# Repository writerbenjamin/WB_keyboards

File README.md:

# WB_keyboards
These are keyboards that I've designed.

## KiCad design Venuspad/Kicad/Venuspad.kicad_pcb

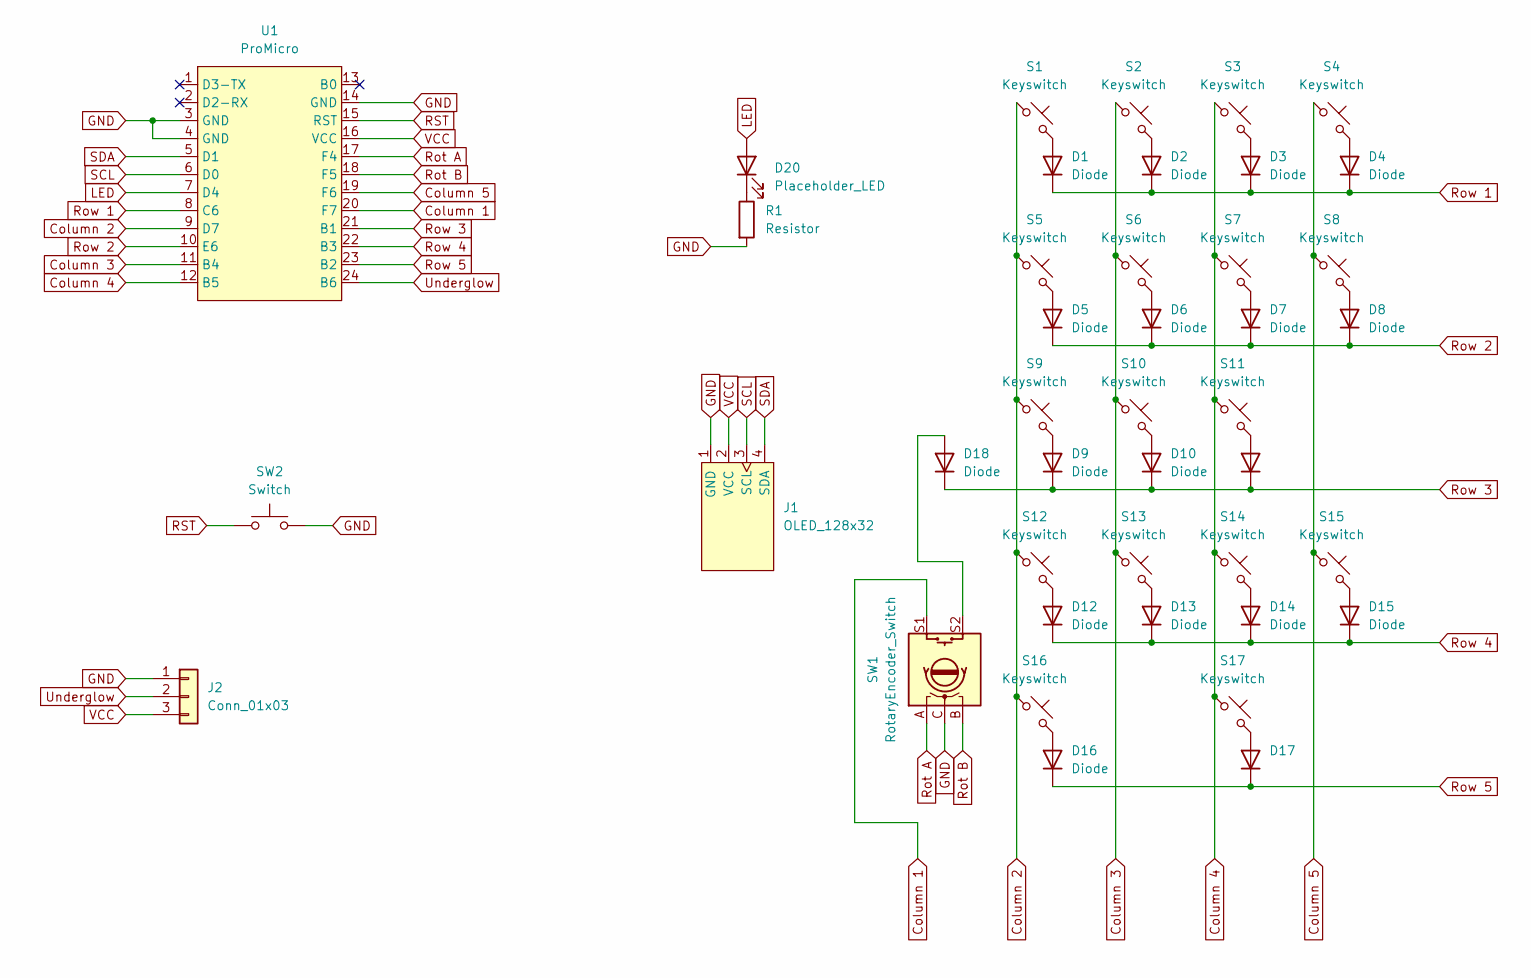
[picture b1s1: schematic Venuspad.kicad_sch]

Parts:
D1, D2, D3, D4, D5, D6, D7, D8, D9, D10, D11, D12, D13, D14, D15, D16, D17, D18: Diode; Diode_DO-35
D20: Placeholder_LED; LED_MX_3mm
J1: OLED_128x32
J2: Conn_01x03; PinHeader_1x03_P2.54mm_Vertical
R1: Resistor; R_Axial_DIN0207_L6.3mm_D2.5mm_P7.62mm_Horizontal
S1, S2, S3, S4, S5, S6, S7, S9, S10, S11, S12, S13, S14, S16: Keyswitch; Hotswap_MX_Plated_1.00u
S8, S15: Keyswitch; Hotswap_MX_Plated_2.00u_90deg
S17: Keyswitch; Hotswap_MX_Plated_2.00u
SW1: RotaryEncoder_Switch; Encoder_EC11_MX
SW2: Switch; Button_TL3342
U1: ProMicro; ProMicro_USBdn

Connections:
Column 1: SW1.S1, U1.20 (F7)
Column 2: S1.1, S5.1, S9.1, S12.1, S16.1, U1.9 (D7)
Column 3: S2.1, S6.1, S10.1, S13.1, U1.11 (B4)
Column 4: S3.1, S7.1, S11.1, S14.1, S17.1, U1.12 (B5)
Column 5: S4.1, S8.1, S15.1, U1.19 (F6)
GND: J1.1 (GND), J2.1, R1.2, SW1.C, SW2.2, U1.3 (GND), U1.4 (GND), U1.14 (GND)
LED: D20.2 (A), U1.7 (D4)
unnamed: D1.2 (A), S1.2
unnamed: D2.2 (A), S2.2
unnamed: D3.2 (A), S3.2
unnamed: D4.2 (A), S4.2
unnamed: D5.2 (A), S5.2
unnamed: D6.2 (A), S6.2
unnamed: D7.2 (A), S7.2
unnamed: D8.2 (A), S8.2
unnamed: D9.2 (A), S9.2
unnamed: D10.2 (A), S10.2
unnamed: D11.2 (A), S11.2
unnamed: D12.2 (A), S12.2
unnamed: D13.2 (A), S13.2
unnamed: D14.2 (A), S14.2
unnamed: D15.2 (A), S15.2
unnamed: D16.2 (A), S16.2
unnamed: D17.2 (A), S17.2
unnamed: D18.2 (A), SW1.S2
unnamed: D20.1 (K), R1.1
RST: SW2.1, U1.15 (RST)
Rot A: SW1.A, U1.17 (F4)
Rot B: SW1.B, U1.18 (F5)
Row 1: D1.1 (K), D2.1 (K), D3.1 (K), D4.1 (K), U1.8 (C6)
Row 2: D5.1 (K), D6.1 (K), D7.1 (K), D8.1 (K), U1.10 (E6)
Row 3: D9.1 (K), D10.1 (K), D11.1 (K), D18.1 (K), U1.21 (B1)
Row 4: D12.1 (K), D13.1 (K), D14.1 (K), D15.1 (K), U1.22 (B3)
Row 5: D16.1 (K), D17.1 (K), U1.23 (B2)
SCL: J1.3 (SCL), U1.6 (D0)
SDA: J1.4 (SDA), U1.5 (D1)
Underglow: J2.2, U1.24 (B6)
VCC: J1.2 (VCC), J2.3, U1.16 (VCC)

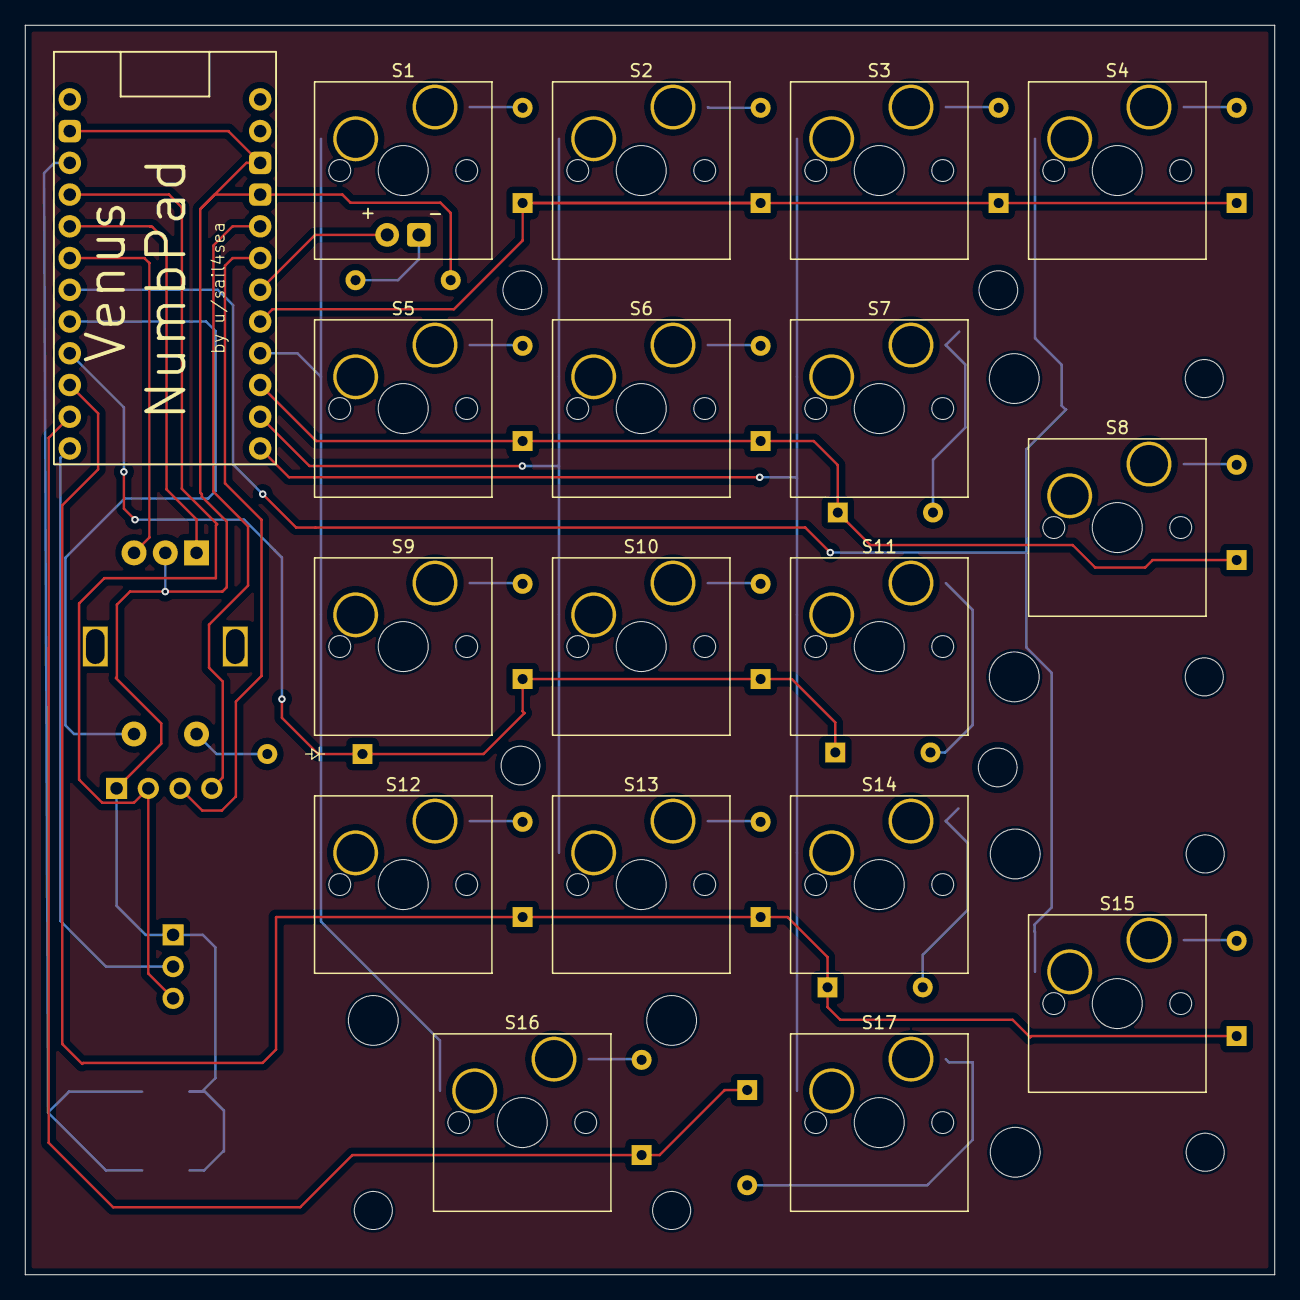
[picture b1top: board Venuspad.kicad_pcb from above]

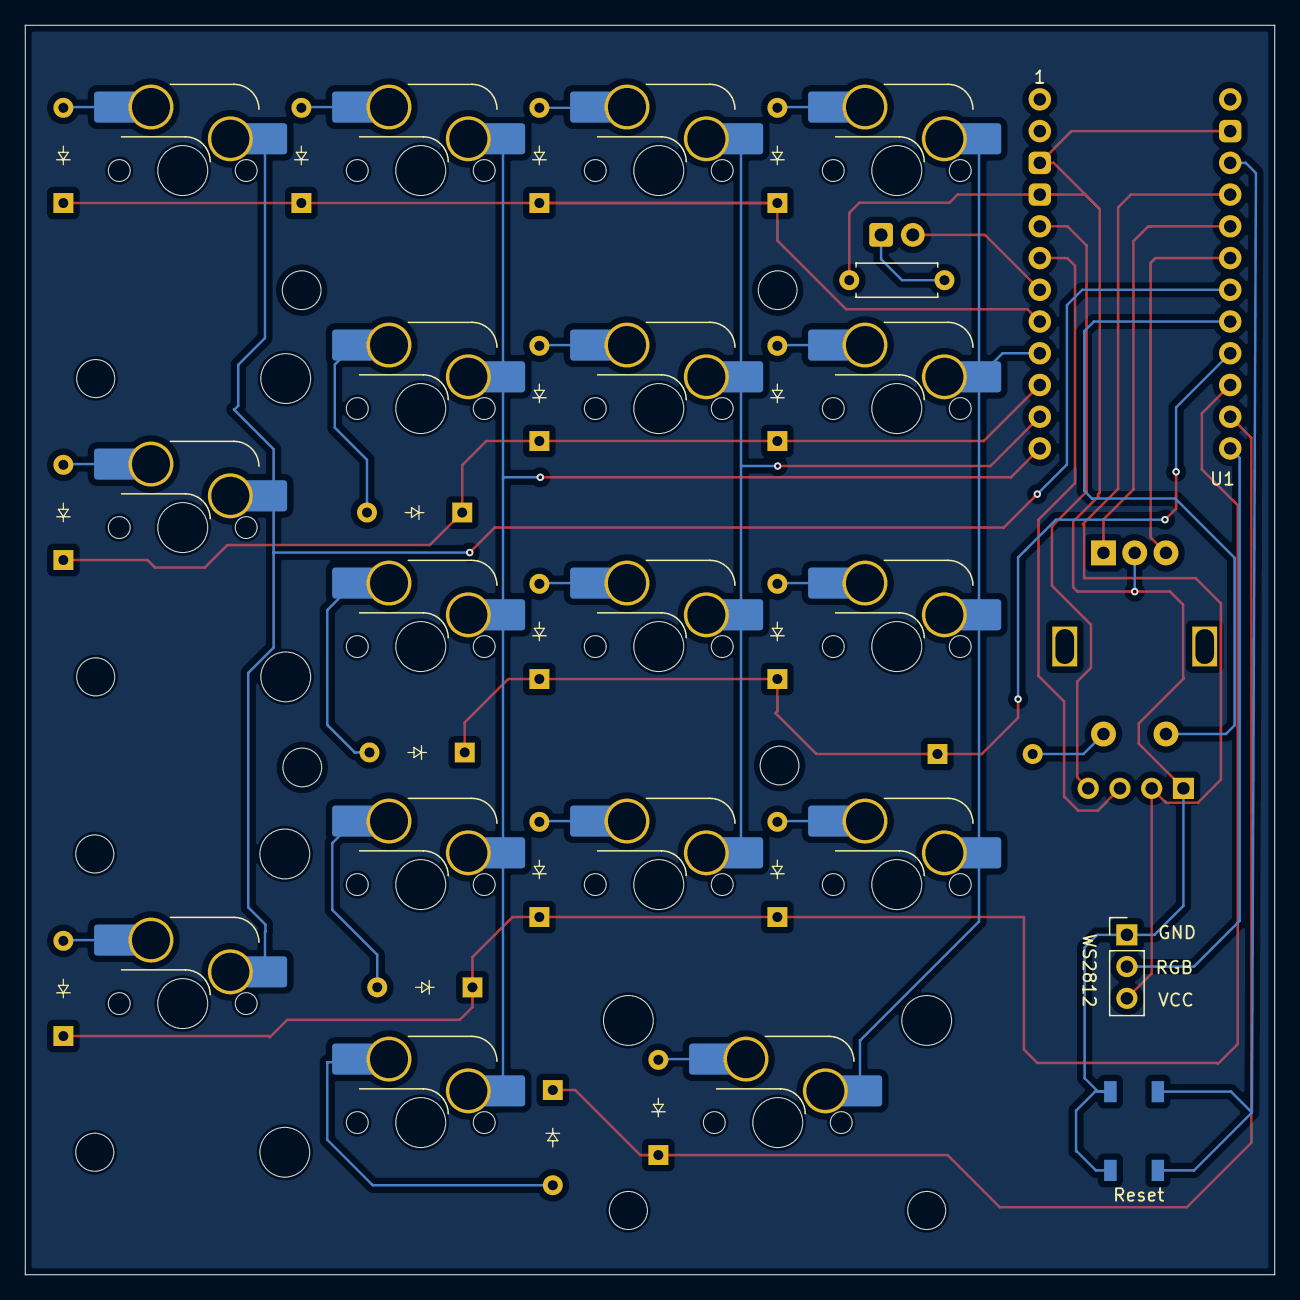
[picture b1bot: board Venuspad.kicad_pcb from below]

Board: 2 copper layers, 100.0 x 100.0 mm, 42 parts (20 on the bottom side), 38 nets.

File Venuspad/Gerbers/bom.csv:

Designator,Footprint,Quantity,Value,LCSC Part #
"D1, D10, D11, D12, D13, D14, D15, D16, D17, D18, D2, D3, D4, D5, D6, D7, D8, D9",Diode_DO-35,18,Diode,
D20,LED_MX_3mm,1,Placeholder_LED,
J1,OLED_128x32,1,OLED_128x32,
J2,PinHeader_1x03_P2.54mm_Vertical,1,Conn_01x03,
R1,R_Axial_DIN0207_L6.3mm_D2.5mm_P7.62mm_Horizontal,1,Resistor,
"S1, S10, S11, S12, S13, S14, S16, S2, S3, S4, S5, S6, S7, S9",Hotswap_MX_Plated_1.00u,14,Keyswitch,
"S15, S8",Hotswap_MX_Plated_2.00u_90deg,2,Keyswitch,
S17,Hotswap_MX_Plated_2.00u,1,Keyswitch,
SW1,Encoder_EC11_MX,1,RotaryEncoder_Switch,
SW2,Button_TL3342,1,Switch,

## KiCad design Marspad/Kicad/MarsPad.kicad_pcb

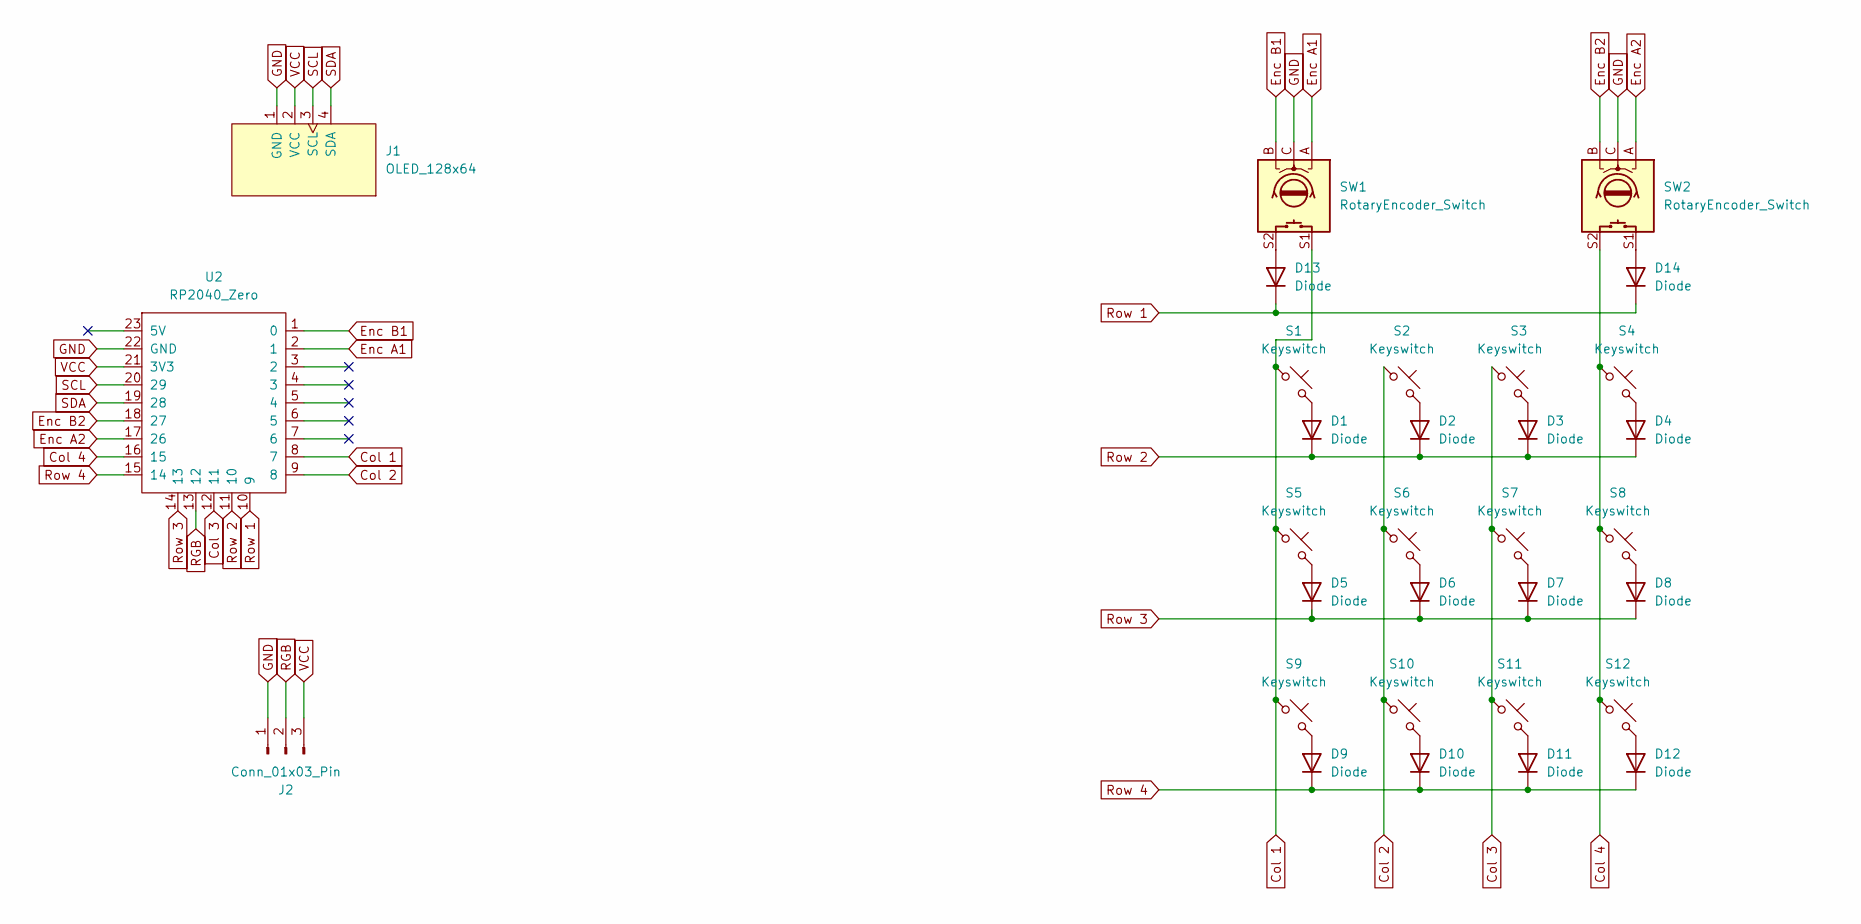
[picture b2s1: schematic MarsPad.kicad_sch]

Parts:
D1, D2, D3, D4, D5, D6, D7, D8, D9, D10, D11, D12, D13, D14: Diode; Diode_DO-35
J1: OLED_128x64; OLED_128x32
J2: Conn_01x03_Pin; PinSocket_1x03_P2.54mm_Vertical
S1, S2, S3, S4, S5, S6, S7, S8, S9, S10, S11, S12: Keyswitch; Hotswap_MX_1.00u
SW1, SW2: RotaryEncoder_Switch; Encoder_EC11_MX
U2: RP2040_Zero

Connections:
Col 1: S1.1, S5.1, S9.1, SW1.S1, U2.8 (7)
Col 2: S2.1, S6.1, S10.1, U2.9 (8)
Col 3: S3.1, S7.1, S11.1, U2.12 (11)
Col 4: S4.1, S8.1, S12.1, SW2.S2, U2.16 (15)
Enc A1: SW1.A, U2.2 (1)
Enc A2: SW2.A, U2.17 (26)
Enc B1: SW1.B, U2.1 (0)
Enc B2: SW2.B, U2.18 (27)
GND: J1.1 (GND), J2.1, SW1.C, SW2.C, U2.22 (GND)
unnamed: D1.2 (A), S1.2
unnamed: D2.2 (A), S2.2
unnamed: D3.2 (A), S3.2
unnamed: D4.2 (A), S4.2
unnamed: D5.2 (A), S5.2
unnamed: D6.2 (A), S6.2
unnamed: D7.2 (A), S7.2
unnamed: D8.2 (A), S8.2
unnamed: D9.2 (A), S9.2
unnamed: D10.2 (A), S10.2
unnamed: D11.2 (A), S11.2
unnamed: D12.2 (A), S12.2
unnamed: D13.2 (A), SW1.S2
unnamed: D14.2 (A), SW2.S1
RGB: J2.2, U2.13 (12)
Row 1: D13.1 (K), D14.1 (K), U2.10 (9)
Row 2: D1.1 (K), D2.1 (K), D3.1 (K), D4.1 (K), U2.11 (10)
Row 3: D5.1 (K), D6.1 (K), D7.1 (K), D8.1 (K), U2.14 (13)
Row 4: D9.1 (K), D10.1 (K), D11.1 (K), D12.1 (K), U2.15 (14)
SCL: J1.3 (SCL), U2.20 (29)
SDA: J1.4 (SDA), U2.19 (28)
VCC: J1.2 (VCC), J2.3, U2.21 (3V3)

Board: 2 copper layers, 31 parts (16 on the bottom side), 31 nets, no tracks yet.

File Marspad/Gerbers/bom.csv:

Designator,Footprint,Quantity,Value,LCSC Part #
"D1, D10, D11, D12, D13, D14, D2, D3, D4, D5, D6, D7, D8, D9",Diode_DO-35,14,Diode,
J1,OLED_128x32,1,OLED_128x64,
J2,PinSocket_1x03_P2.54mm_Vertical,1,Conn_01x03_Pin,
"S1, S10, S11, S12, S2, S3, S4, S5, S6, S7, S8, S9",Hotswap_MX_1.00u,12,Keyswitch,
"SW1, SW2",Encoder_EC11_MX,2,RotaryEncoder_Switch,
U2,RP2040_Zero,1,RP2040_Zero,

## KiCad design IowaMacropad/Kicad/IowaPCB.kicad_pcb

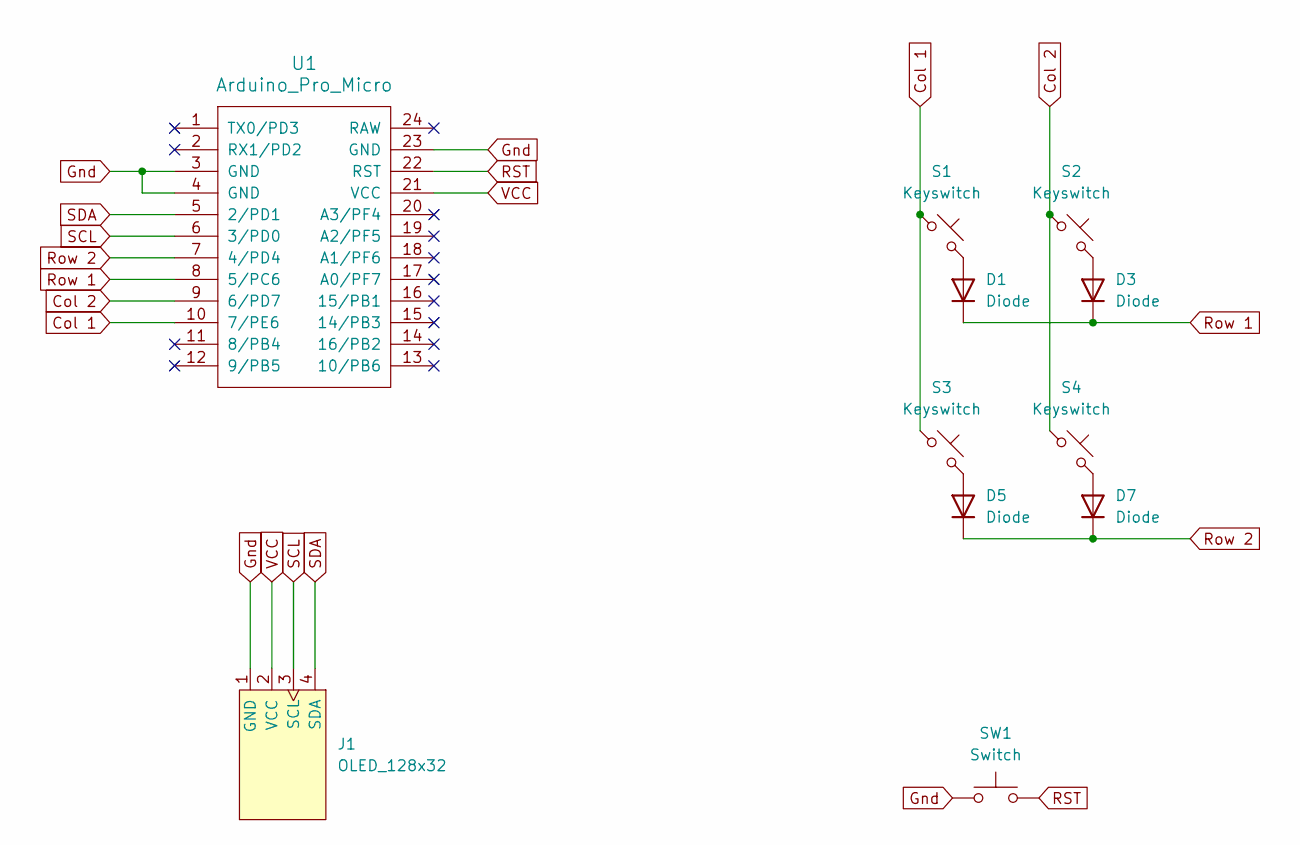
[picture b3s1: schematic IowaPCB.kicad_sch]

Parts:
D1, D3, D5, D7: Diode; Diode_DO-35
J1: OLED_128x32
S1: Keyswitch; MX_Plate_ISOEnter_180deg
S2, S3: Keyswitch; MX_PCB_1.00u
S4: Keyswitch; MX_Plate_ISOEnter
SW1: Switch; Button_TL3342
U1: Arduino_Pro_Micro

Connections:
Col 1: S1.1, S3.1, U1.10 (7/PE6)
Col 2: S2.1, S4.1, U1.9 (6/PD7)
Gnd: J1.1 (GND), SW1.1, U1.3 (GND), U1.4 (GND), U1.23 (GND)
unnamed: D1.2 (A), S1.2
unnamed: D3.2 (A), S2.2
unnamed: D5.2 (A), S3.2
unnamed: D7.2 (A), S4.2
RST: SW1.2, U1.22 (RST)
Row 1: D1.1 (K), D3.1 (K), U1.8 (5/PC6)
Row 2: D5.1 (K), D7.1 (K), U1.7 (4/PD4)
SCL: J1.3 (SCL), U1.6 (3/PD0)
SDA: J1.4 (SDA), U1.5 (2/PD1)
VCC: J1.2 (VCC), U1.21 (VCC)

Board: 2 copper layers, 11 parts (6 on the bottom side), 13 nets, no tracks yet.

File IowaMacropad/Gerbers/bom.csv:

Designator,Footprint,Quantity,Value,LCSC Part #
"D1, D3, D5, D7",Diode_DO-35,4,Diode,
J1,OLED_128x32,1,OLED_128x32,
S1,MX_Plate_ISOEnter_180deg,1,Keyswitch,
"S2, S3",MX_PCB_1.00u,2,Keyswitch,
S4,MX_Plate_ISOEnter,1,Keyswitch,
SW1,Button_TL3342,1,Switch,
U1,Arduino_Pro_Micro,1,Arduino_Pro_Micro,

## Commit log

2025-06-07 Initial commit of the Iowa Macropad, an Iowa shaped macropad that uses ISO Enters.
2025-06-07 made a PCB for a 12 key macropad with two rotary encoders and a 128x32 oled display.
2025-06-07 Fixed error where silkscreen was mirrored for my name and credits.
2025-06-11 added header for WS2812 led strips
2025-06-11 added RGB headers for WS2812 LEDs and fixed other artifacts.
2025-06-14 Created Venuspad, A numpad with Rotoray, encoder, oled, and RGB underglow. Also has an LED for Numlock.
